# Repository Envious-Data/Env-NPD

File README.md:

# Env-NPD
A Raspberry Pi Pico powered Numpad!

### What is this?
This is another RPI Pico type mechanical board thing alike my other project but a entirely seperate numpad!

This will use KMK and CircuitPython and should be incredibly easy to build.

### Parts List
* 1x Raspberry Pi Pico
* 17x Keyboard Switches of your choosing
* 17x 1N4148 Diodes (through hole)
* Numpad Keycap set
* Numpad PCB

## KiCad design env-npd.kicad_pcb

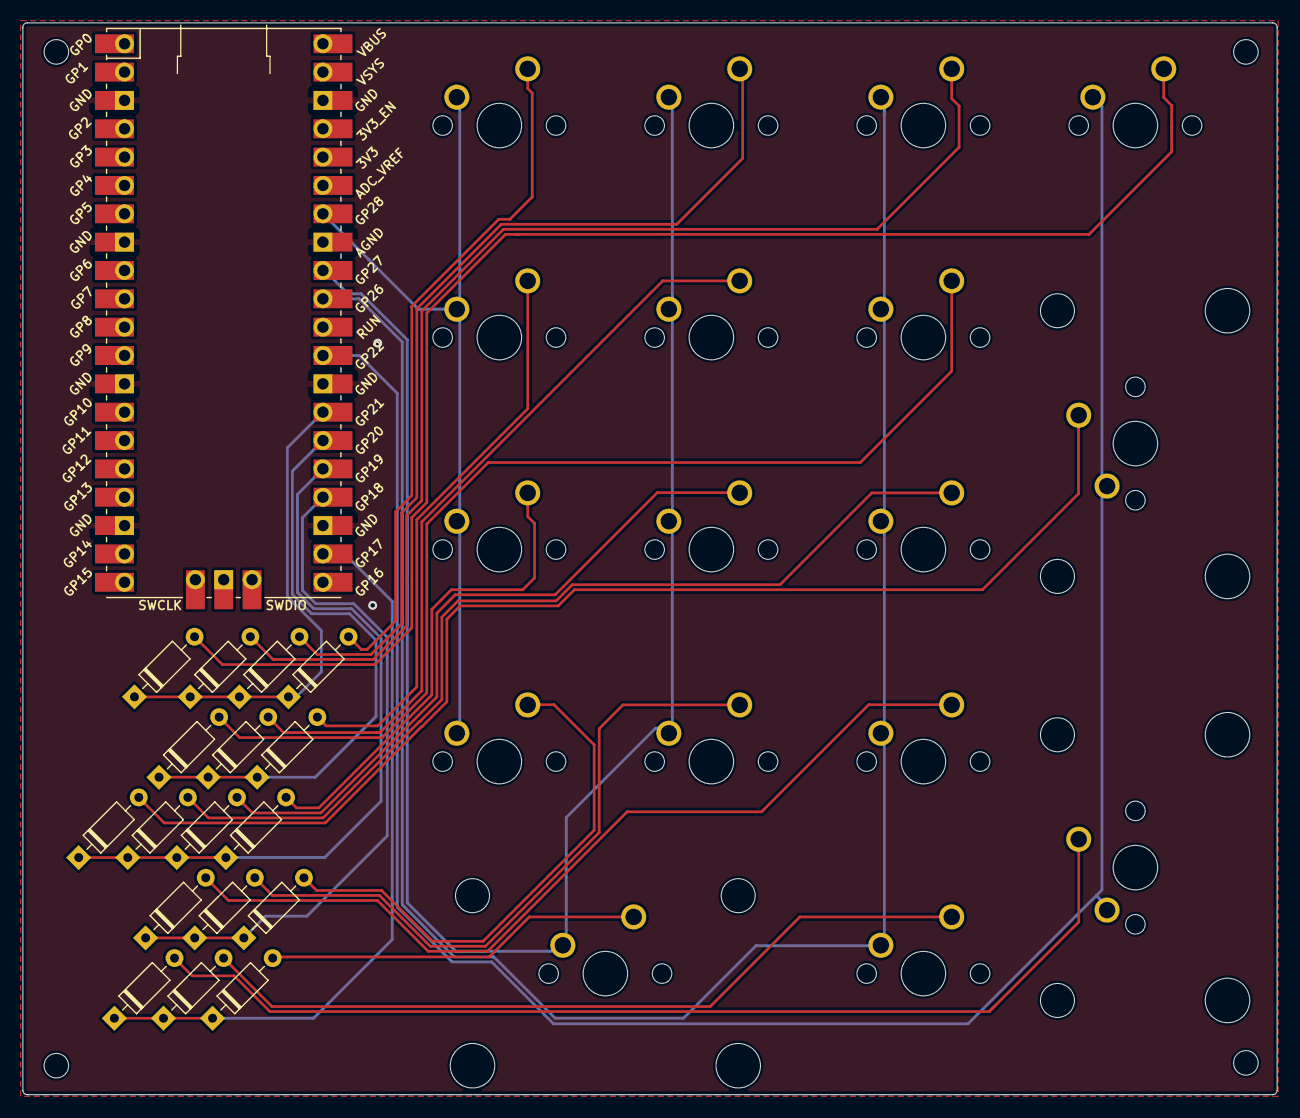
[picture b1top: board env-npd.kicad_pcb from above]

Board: 2 copper layers, 112.4 x 96.0 mm, 39 parts (0 on the bottom side), 27 nets.

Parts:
D1, D2, D3, D4, D5, D6, D7, D8, D9, D10, D11, D12, D13, D14, D15, D16, D17: D_Small; D_DO-35_SOD27_P7.62mm_Horizontal
H1, H2, H3, H4: MountingHole; MountingHole_2.2mm_M2
MCU1: Pico; RPi_Pico_SMD_TH
MX1, MX2, MX3, MX4, MX5, MX6, MX7, MX8, MX9, MX10, MX12, MX13, MX14, MX16: MX-NoLED; MXOnly-1U-NoLED
MX11, MX15, MX17: MX-NoLED; MXOnly-2U-NoLED

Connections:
GND: MCU1.3, MCU1.8, MCU1.13, MCU1.18, MCU1.23, MCU1.28, MCU1.33, MCU1.38
unnamed: D1.2, MX1.2
unnamed: D2.2, MX2.2
unnamed: D3.2, MX3.2
unnamed: D4.2, MX4.2
unnamed: D5.2, MX5.2
unnamed: D6.2, MX6.2
unnamed: D7.2, MX7.2
unnamed: D8.2, MX8.2
unnamed: D9.2, MX9.2
unnamed: D10.2, MX10.2
unnamed: D11.2, MX11.2
unnamed: D12.2, MX12.2
unnamed: D13.2, MX13.2
unnamed: D14.2, MX14.2
unnamed: D15.2, MX15.2
unnamed: D16.2, MX16.2
unnamed: D17.2, MX17.2
col0: MCU1.34, MX1.1, MX5.1, MX8.1, MX12.1
col1: MCU1.32, MX2.1, MX6.1, MX9.1, MX13.1, MX15.1
col2: MCU1.31, MX3.1, MX7.1, MX10.1, MX14.1, MX16.1
col3: MCU1.29, MX4.1, MX11.1, MX17.1
row0: D1.1, D2.1, D3.1, D4.1, MCU1.27
row1: D5.1, D6.1, D7.1, MCU1.26
row2: D8.1, D9.1, D10.1, D11.1, MCU1.25
row3: D12.1, D13.1, D14.1, MCU1.24
row4: D15.1, D16.1, D17.1, MCU1.22

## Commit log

2021-04-11 Initial commit +1
2021-04-11 Small changes, updated readme
2021-04-11 Beginnings of an acrylic sandwich case
2021-04-11 Added image
2021-04-11 adjusted size and removed TP pads
    TP pads aren't needed and they are way too close together, they may cause issues with a PCB manufacturer whos tolerances are looser than JLCPCBs
2021-04-11 Added lines for plate design.
2021-09-20 I couldn't sleep so I re-designed the pcb a bit and may actually order some for my self (since I need me a numpad)
2021-09-20 added a silkscreen design and generated gerbers
2022-01-10 updated design, added outlines for a basic case on Eco1.user and Eco2.user
2022-01-10 Generated Updated gerber and exported DXFs for top and bottom plate.
2022-01-10 couple more update bits
